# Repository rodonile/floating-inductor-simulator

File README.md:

# floating-inductor-simulator
PCB design (KiCAD) of a floating inductor simulator circuit, based on the [Grueningen Synthetic Inductor Circuit](https://ieeexplore.ieee.org/document/1457733). The inductance can be changed via the trim potentiometer (RV1). The circuit with the selected components can be used to simulate inductors up to 80H. 

Formula for determining the inductance value of the circuit:

        L = R2^2 * RV1 * C4 / R7,   given R2 = R3 = R4

The desired value range of the inductance can be tweaked by changing the resistors/caps/pots values. For example, with the values on the schematic below and with a 10kOhm RV1 trim potentiometer we are able to simulate inductances ranging from 20mH to 7.7H. With a 100kOhm RV1 potentiometer the circuit can simulate inductances up to 80H.

The frequency operation range of the circuit spans from ~100Hz to ~10kHz. For signals near and outside this range the circuits starts being unstable.

The RV2 potentiometer is a series resistor that can be used to adjust the Q-factor of the circuit but has no influence on the inductance value.

## Schematics

## Layout and 3D view

Kicad project files are available in the [kicad](./kicad) folder.

3D view TOP                |  3D view BOTTOM
:-------------------------:|:-------------------------:
  |  

## Bill of materials (BOM)

The bill of material is also available in the [ibom.html](https://raw.githubusercontent.com/rodonile/floating-inductor-simulator/main/ibom.html) file (interactive html format, to be opened with a web browser). The components I used to build the circuit are available as a [csv file](components-digikey.csv) (they were ordered from Digikey).

## Gerbers
Gerber files are available in [releases](https://github.com/rodonile/floating-inductor-simulator/releases). The board is a 4-layer PCB. Designed with JSCPCB design rules.

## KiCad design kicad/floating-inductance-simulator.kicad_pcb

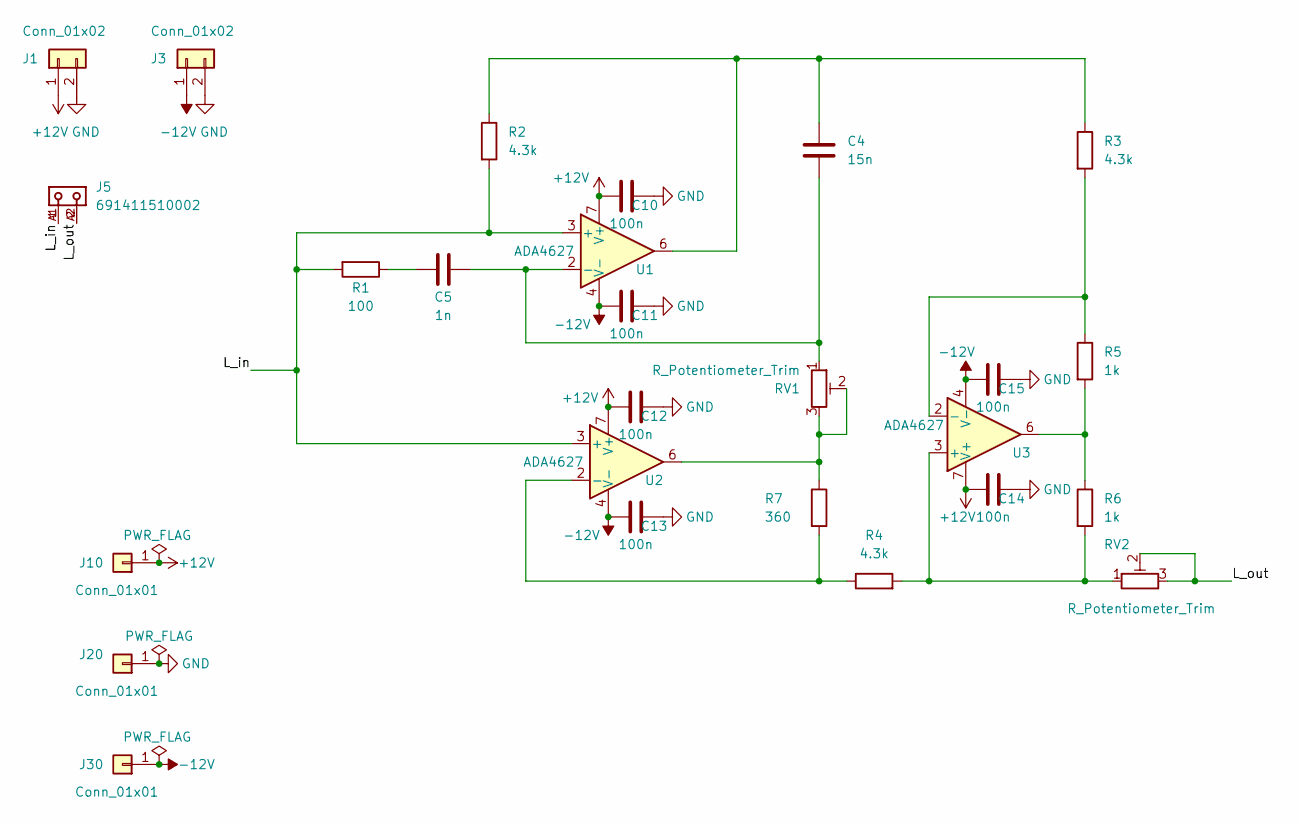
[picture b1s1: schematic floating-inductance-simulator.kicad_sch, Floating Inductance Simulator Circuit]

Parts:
C4: 15n; C_1210_3225Metric_Pad1.33x2.70mm_HandSolder
C5: 1n; C_1210_3225Metric_Pad1.33x2.70mm_HandSolder
C10, C11, C12, C13, C14, C15: 100n; C_1210_3225Metric_Pad1.33x2.70mm_HandSolder
J1, J3: Conn_01x02; Samtec_PinHeader_1x02
J5: 691411510002; PART-NUMBER 691411510002
J10, J20, J30: Conn_01x01; CalTest_CT3151_small
R1: 100; R_2010_5025Metric_Pad1.40x2.65mm_HandSolder
R2, R3, R4: 4.3k; R_2010_5025Metric_Pad1.40x2.65mm_HandSolder
R5, R6: 1k; R_2010_5025Metric_Pad1.40x2.65mm_HandSolder
R7: 360; R_2010_5025Metric_Pad1.40x2.65mm_HandSolder
RV1, RV2: R_Potentiometer_Trim; Potentiometer_Bourns_3006P_Horizontal
U1, U2, U3: ADA4627; SOIC-8_3.9x4.9mm_P1.27mm

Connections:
+12V: C10.1, C12.1, C14.1, J1.1, J10.1, U1.7 (V+), U2.7 (V+), U3.7 (V+)
-12V: C11.1, C13.1, C15.1, J3.1, J30.1, U1.4 (V-), U2.4 (V-), U3.4 (V-)
/L_in: J5.1, J5.A1, R1.2, R2.2, U1.3 (+), U2.3 (+)
/L_out: J5.2, J5.A2, RV2.2, RV2.3
GND: C10.2, C11.2, C12.2, C13.2, C14.2, C15.2, J1.2, J3.2, J20.1
unnamed: C4.1, R2.1, R3.1, U1.6
unnamed: C4.2, C5.2, RV1.1, U1.2 (-)
unnamed: C5.1, R1.1
unnamed: R3.2, R5.1, U3.2 (-)
unnamed: R4.1, R7.2, U2.2 (-)
unnamed: R4.2, R6.2, RV2.1, U3.3 (+)
unnamed: R5.2, R6.1, U3.6
unnamed: R7.1, RV1.2, RV1.3, U2.6

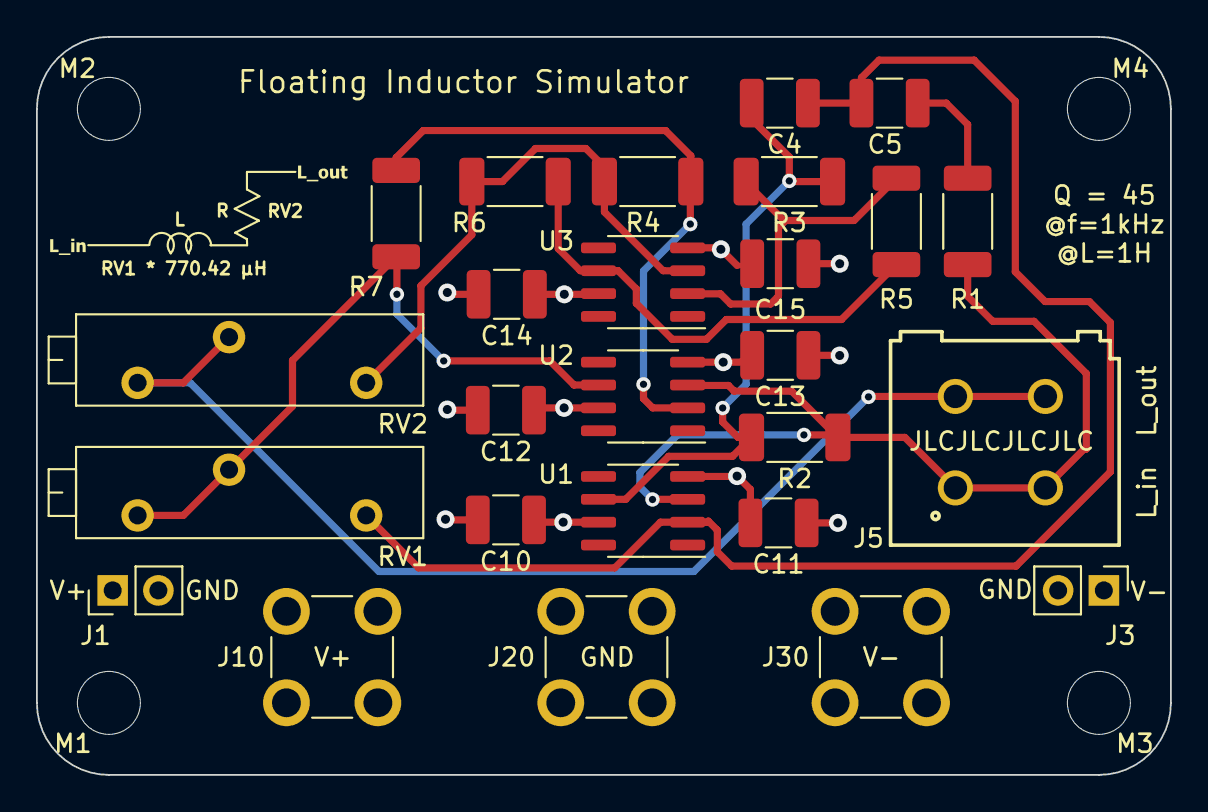
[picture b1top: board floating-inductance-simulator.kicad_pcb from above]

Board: 4 copper layers, 63.0 x 41.0 mm, 30 parts (0 on the bottom side), 13 nets.

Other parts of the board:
M1, M2, M3, M4: MountingHole_3.5mm

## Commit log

2022-07-28 Create LICENSE
2022-07-28 upload readme
2022-07-28 uploade BOM
2022-07-28 upload png bom
2022-07-28 fix releases link
2022-07-28 upload digikey component list
2022-07-28 add kicad project and libraries
2022-07-29 change readme
